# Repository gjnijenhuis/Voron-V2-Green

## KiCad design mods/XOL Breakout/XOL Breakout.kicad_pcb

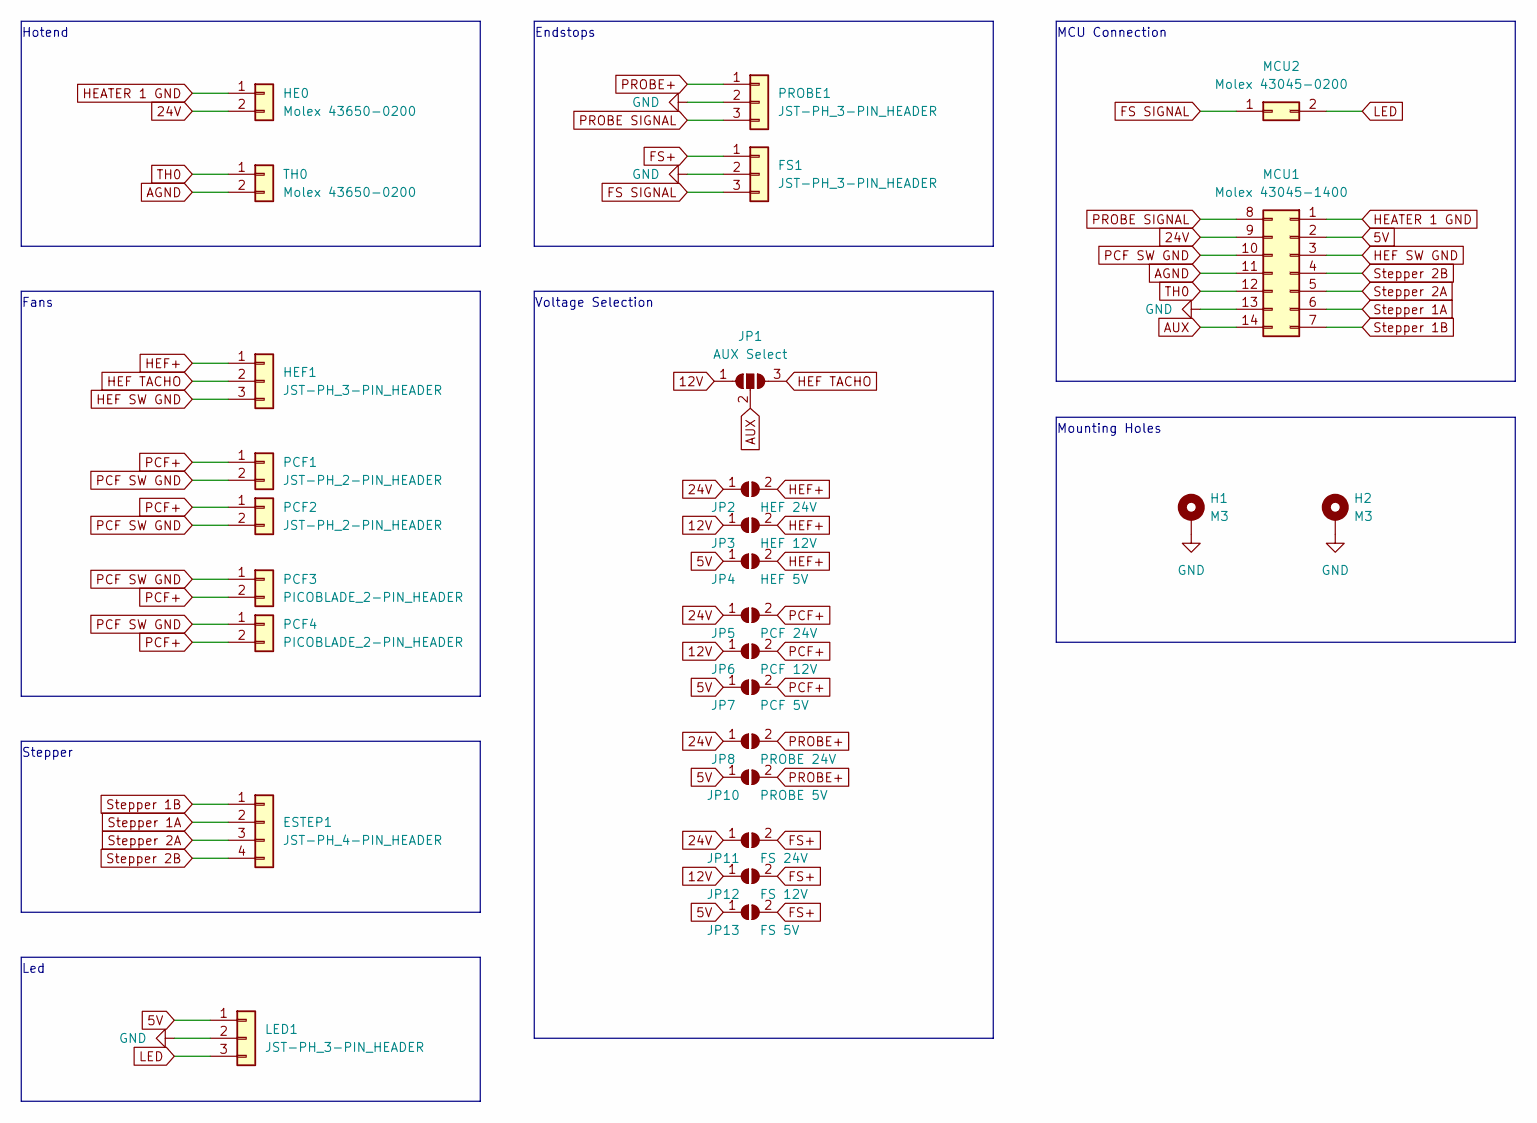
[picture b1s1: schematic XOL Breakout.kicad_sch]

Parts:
ESTEP1: JST-PH_4-PIN_HEADER; JST_PH_B4B-PH-K_1x04_P2.00mm_Vertical
FS1: JST-PH_3-PIN_HEADER; JST_PH_B3B-PH-K_1x03_P2.00mm_Vertical
H1, H2: M3; MountingHole_3.2mm_M3_DIN965_Pad
HE0: Molex 43650-0200; Molex_Micro-Fit_3.0_43650-0200_1x02_P3.00mm_Horizontal
HEF1: JST-PH_3-PIN_HEADER; JST_PH_B3B-PH-K_1x03_P2.00mm_Vertical
JP1: AUX Select; SolderJumper-3_P2.0mm_Open_TrianglePad1.0x1.5mm
JP2: HEF 24V; SolderJumper-2_P1.3mm_Open_TrianglePad1.0x1.5mm
JP3: HEF 12V; SolderJumper-2_P1.3mm_Open_TrianglePad1.0x1.5mm
JP4: HEF 5V; SolderJumper-2_P1.3mm_Open_TrianglePad1.0x1.5mm
JP5: PCF 24V; SolderJumper-2_P1.3mm_Open_TrianglePad1.0x1.5mm
JP6: PCF 12V; SolderJumper-2_P1.3mm_Open_TrianglePad1.0x1.5mm
JP7: PCF 5V; SolderJumper-2_P1.3mm_Open_TrianglePad1.0x1.5mm
JP8: PROBE 24V; SolderJumper-2_P1.3mm_Open_TrianglePad1.0x1.5mm
JP10: PROBE 5V; SolderJumper-2_P1.3mm_Open_TrianglePad1.0x1.5mm
JP11: FS 24V; SolderJumper-2_P1.3mm_Open_TrianglePad1.0x1.5mm
JP12: FS 12V; SolderJumper-2_P1.3mm_Open_TrianglePad1.0x1.5mm
JP13: FS 5V; SolderJumper-2_P1.3mm_Open_TrianglePad1.0x1.5mm
LED1: JST-PH_3-PIN_HEADER; JST_PH_B3B-PH-K_1x03_P2.00mm_Vertical
MCU1: Molex 43045-1400; Molex_Micro-Fit_3.0_43045-1400_2x07_P3.00mm_Horizontal
MCU2: Molex 43045-0200; Molex_Micro-Fit_3.0_43045-0200_2x01_P3.00mm_Horizontal
PCF1, PCF2: JST-PH_2-PIN_HEADER; JST_PH_B2B-PH-K_1x02_P2.00mm_Vertical
PCF3, PCF4: PICOBLADE_2-PIN_HEADER; Molex_PicoBlade_53047-0210_1x02_P1.25mm_Vertical
PROBE1: JST-PH_3-PIN_HEADER; JST_PH_B3B-PH-K_1x03_P2.00mm_Vertical
TH0: Molex 43650-0200; Molex_Micro-Fit_3.0_43650-0200_1x02_P3.00mm_Horizontal

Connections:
5V: JP4.1 (A), JP7.1 (A), JP10.1 (A), JP13.1 (A), LED1.1, MCU1.2
12V: JP1.1 (A), JP3.1 (A), JP6.1 (A), JP12.1 (A)
24V: HE0.2, JP2.1 (A), JP5.1 (A), JP8.1 (A), JP11.1 (A), MCU1.9
AGND: MCU1.11, TH0.2
AUX: JP1.2 (C), MCU1.14
FS SIGNAL: FS1.3, MCU2.1
FS+: FS1.1, JP11.2 (B), JP12.2 (B), JP13.2 (B)
GND: FS1.2, H1.1, H2.1, LED1.2, MCU1.13, PROBE1.2
HEATER 1 GND: HE0.1, MCU1.1
HEF SW GND: HEF1.3, MCU1.3
HEF TACHO: HEF1.2, JP1.3 (B)
HEF+: HEF1.1, JP2.2 (B), JP3.2 (B), JP4.2 (B)
LED: LED1.3, MCU2.2
PCF SW GND: MCU1.10, PCF1.2, PCF2.2, PCF3.1, PCF4.1
PCF+: JP5.2 (B), JP6.2 (B), JP7.2 (B), PCF1.1, PCF2.1, PCF3.2, PCF4.2
PROBE SIGNAL: MCU1.8, PROBE1.3
PROBE+: JP8.2 (B), JP10.2 (B), PROBE1.1
Stepper 1A: ESTEP1.2, MCU1.6
Stepper 1B: ESTEP1.1, MCU1.7
Stepper 2A: ESTEP1.3, MCU1.5
Stepper 2B: ESTEP1.4, MCU1.4
TH0: MCU1.12, TH0.1

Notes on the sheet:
MCU Connection
Endstops
Hotend
Mounting Holes
Led
Stepper
Fans
Voltage Selection

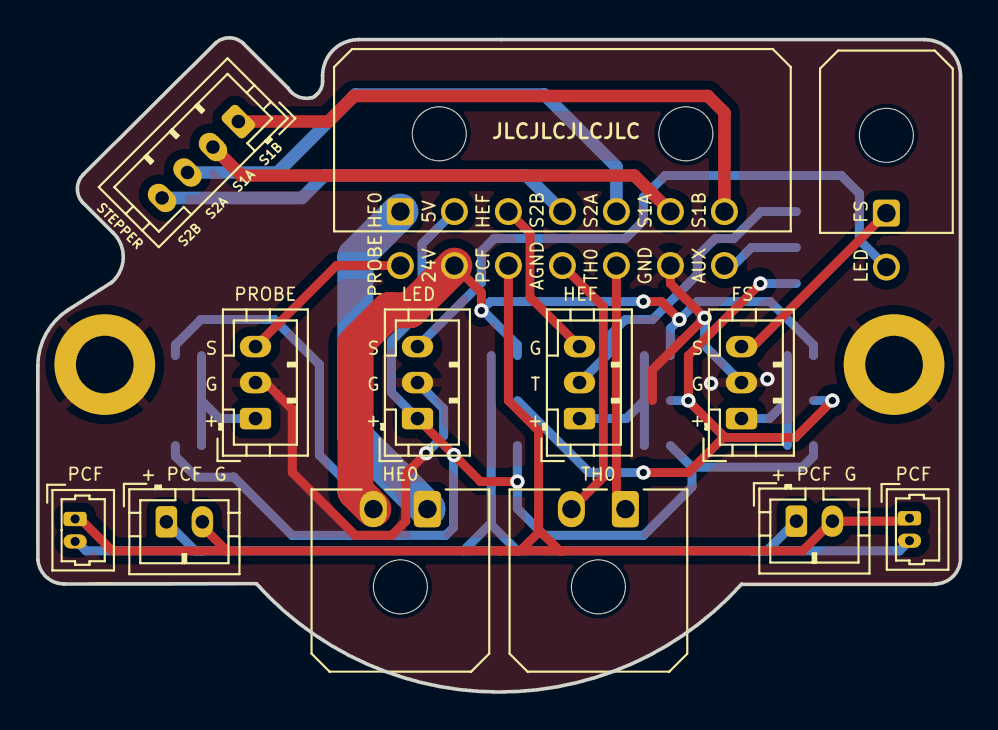
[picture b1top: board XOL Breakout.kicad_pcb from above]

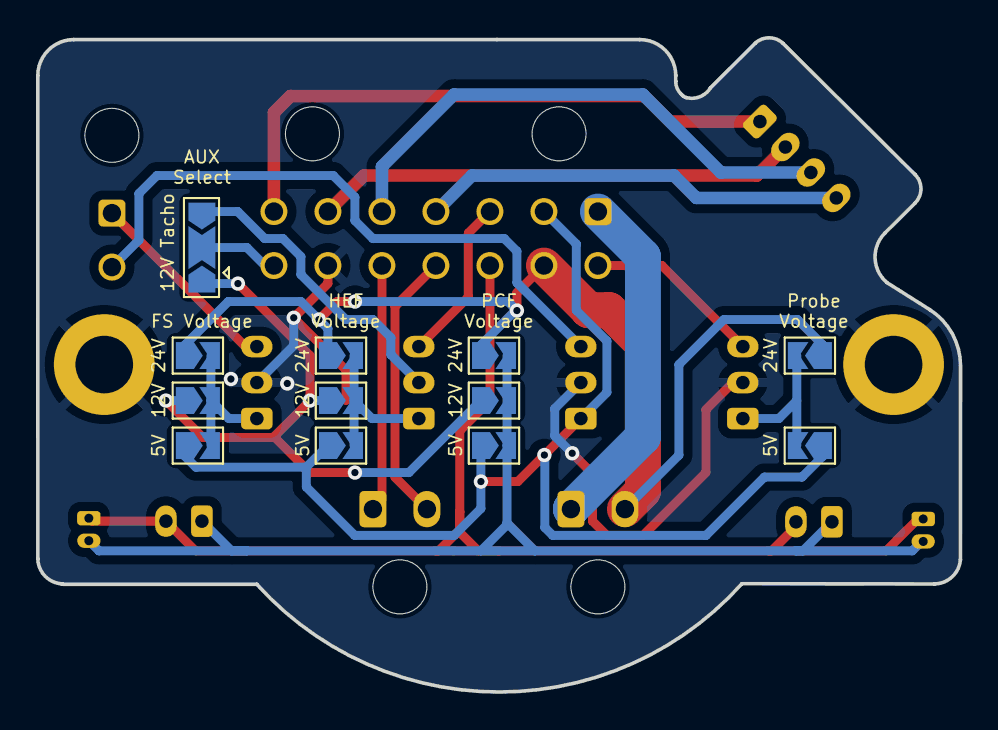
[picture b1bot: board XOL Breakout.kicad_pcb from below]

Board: 2 copper layers, 51.3 x 36.3 mm, 27 parts (12 on the bottom side), 22 nets.

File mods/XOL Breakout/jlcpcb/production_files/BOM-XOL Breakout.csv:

Comment,Designator,Footprint,LCSC
PICOBLADE_2-PIN_HEADER,"PCF3,PCF4",Molex_PicoBlade_53047-0210_1x02_P1.25mm_Vertical,C114130
Molex 43045-0200,MCU2,Molex_Micro-Fit_3.0_43045-0200_2x01_P3.00mm_Horizontal,C122431
JST-PH_4-PIN_HEADER,ESTEP1,JST_PH_B4B-PH-K_1x04_P2.00mm_Vertical,C131334
JST-PH_2-PIN_HEADER,"PCF1,PCF2",JST_PH_B2B-PH-K_1x02_P2.00mm_Vertical,C131337
JST-PH_3-PIN_HEADER,"FS1,HEF1,LED1,PROBE1",JST_PH_B3B-PH-K_1x03_P2.00mm_Vertical,C131339
Molex 43650-0200,"HE0,TH0",Molex_Micro-Fit_3.0_43650-0200_1x02_P3.00mm_Horizontal,C192562
Molex 43045-1400,MCU1,Molex_Micro-Fit_3.0_43045-1400_2x07_P3.00mm_Horizontal,C477050
FS 5V,JP13,SolderJumper-2_P1.3mm_Open_TrianglePad1.0x1.5mm,
FS 12V,JP12,SolderJumper-2_P1.3mm_Open_TrianglePad1.0x1.5mm,
FS 24V,JP11,SolderJumper-2_P1.3mm_Open_TrianglePad1.0x1.5mm,
PROBE 5V,JP10,SolderJumper-2_P1.3mm_Open_TrianglePad1.0x1.5mm,
PROBE 24V,JP8,SolderJumper-2_P1.3mm_Open_TrianglePad1.0x1.5mm,
PCF 5V,JP7,SolderJumper-2_P1.3mm_Open_TrianglePad1.0x1.5mm,
PCF 12V,JP6,SolderJumper-2_P1.3mm_Open_TrianglePad1.0x1.5mm,
PCF 24V,JP5,SolderJumper-2_P1.3mm_Open_TrianglePad1.0x1.5mm,
HEF 5V,JP4,SolderJumper-2_P1.3mm_Open_TrianglePad1.0x1.5mm,
HEF 12V,JP3,SolderJumper-2_P1.3mm_Open_TrianglePad1.0x1.5mm,
HEF 24V,JP2,SolderJumper-2_P1.3mm_Open_TrianglePad1.0x1.5mm,
AUX Select,JP1,SolderJumper-3_P2.0mm_Open_TrianglePad1.0x1.5mm,
M3,H1,MountingHole_3.2mm_M3_DIN965_Pad,
M3,H2,MountingHole_3.2mm_M3_DIN965_Pad,

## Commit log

2023-08-07 create repository
2023-08-07 New backup from 07-08-23
2023-08-08 New backup from 08-08-23
2023-08-16 Create BUILD.md
    Added build description
2023-08-16 Added XOL PCB to the repo
2023-08-16 Update BUILD.md
    Added XOL PCB link to the build file
